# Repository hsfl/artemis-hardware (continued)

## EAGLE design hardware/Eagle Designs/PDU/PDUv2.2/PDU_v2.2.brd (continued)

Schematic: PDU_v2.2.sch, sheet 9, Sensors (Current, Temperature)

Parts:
C8, C29, C30, C37, C42, C61, C68, C69, C70, C71: 0.1 uF; 0805
C82: 0.1 uF; 0603-CAP
R26, R34, R36, R52, R54, R64, R65, R67, R76, R78: 3.3 k; 0805
R35, R39, R63, R66, R79, R80, R81, R84, R85, R88: 10; 0805
R53, R77, R87, R89, R90: 2 m; 0805
R61: 45.3 k; 0603-RES
R62: 10 k; 0603-RES
U15, U30, U31, U32, U33: INA219BIDR; SOIC127P599X175-8N
U18: TMP36FSZ; R_8_ADI

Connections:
AIN1: R61.1, R62.2; also elsewhere on the board
BUS_3V3: C8.1, C68.1, C69.1, C70.1, C71.1, C82.2, R26.1, R34.1, R36.1, R52.1, R54.1, R64.1, R65.1, R67.1, R76.1, R78.1, U15.1 (A1), U15.5 (VS), U18.5 (!SHUTDOWN), U18.8 (+VS), U30.5 (VS), U31.2 (A0), U31.5 (VS), U32.5 (VS), U33.5 (VS); also elsewhere on the board
CS_SOL1_VIN+: C30.1, R63.1, U30.8 (VIN+)
CS_SOL1_VIN-: C30.2, R66.1, U30.7 (VIN-)
CS_SOL2_VIN+: C37.1, R79.1, U31.8 (VIN+)
CS_SOL2_VIN-: C37.2, R80.1, U31.7 (VIN-)
CS_SOL3_VIN+: C42.1, R81.1, U32.8 (VIN+)
CS_SOL3_VIN-: C42.2, R88.1, U32.7 (VIN-)
CS_SOL4_VIN+: C61.1, R84.1, U33.8 (VIN+)
CS_SOL4_VIN-: C61.2, R85.1, U33.7 (VIN-)
CS_VBATT: R35.2, R53.2; also elsewhere on the board
CS_VBATT_VIN+: C29.1, R35.1, U15.8 (VIN+)
CS_VBATT_VIN-: C29.2, R39.1, U15.7 (VIN-)
GND: C8.2, C68.2, C69.2, C70.2, C71.2, C82.1, R62.1, U15.2 (A0), U15.6 (GND), U18.4 (GND), U30.1 (A1), U30.2 (A0), U30.6 (GND), U31.1 (A1), U31.6 (GND), U32.1 (A1), U32.6 (GND), U33.1 (A1), U33.6 (GND); also elsewhere on the board
I2C1_SCL: R36.2, R54.2, R64.2, R67.2, R78.2, U15.4 (SCL), U30.4 (SCL), U31.4 (SCL), U32.4 (SCL), U33.2 (A0), U33.4 (SCL); also elsewhere on the board
I2C1_SDA: R26.2, R34.2, R52.2, R65.2, R76.2, U15.3 (SDA), U30.3 (SDA), U31.3 (SDA), U32.2 (A0), U32.3 (SDA), U33.3 (SDA); also elsewhere on the board
unnamed: R61.2, U18.1 (VOUT)
SOLAR_IN1: R63.2, R77.2; also elsewhere on the board
SOLAR_IN1_LOAD: R66.2, R77.1; also elsewhere on the board
SOLAR_IN2: R79.2, R87.2; also elsewhere on the board
SOLAR_IN2_LOAD: R80.2, R87.1; also elsewhere on the board
SOLAR_IN3: R81.2, R89.2; also elsewhere on the board
SOLAR_IN3_LOAD: R88.2, R89.1; also elsewhere on the board
SOLAR_IN4: R84.2, R90.2; also elsewhere on the board
SOLAR_IN4_LOAD: R85.2, R90.1; also elsewhere on the board
VBATT: R39.2, R53.1; also elsewhere on the board

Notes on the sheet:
All cap/res in current sensor circuit is 0805 size.
All cap/res in temp sensor is 0603 size.
Analog Temperature Sensor
Current Sensor (VBATT)
Current Sensor (Solar Panels)

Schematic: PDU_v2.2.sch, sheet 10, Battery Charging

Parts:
C10, C12, C18, C91: 0.1 uF; 0805
C14, C39: 10 uF; 0805
C38: 4.7 uF; 0805
C40, C41: 1 uF; 0805
D1: CMDSH-3TR; SOD2512X110N
D3, D5: MBR230S1F; CR_0LSFT1G_ONS
D6, D7, D8, D9, D10, D11, D12: PMEG10020ELRX; CFP3_SOD123W_NEX
D13: LED_0805
J18: 5037630491; CON_5037630491
L2: AIML-0805-150K-T; AIML-0805_ABR
R27: 3 k; 0805
R28: 6.04 k; 0805
R29: 0; 0805
R37: 26.7 k; 0805
R55: 169 k; 0805
R56: 28.4k; 0603-RES
R91, R95: 1; 0805
R92, R94: 3.01 k; 0805
R96: 5.1 k; 0805
U20: LTC4012IUFPBF; QFN50P400X400X80-21N
U28: SI4431BDY-T1-E3; SOIC-8_SI
U29: AO4818B; SOIC8_NARROW_VIS

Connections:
5V_USB_CHRG: D12.2 (12); also elsewhere on the board
BATT_CHRG: C39.1, D5.1, R94.2, R95.1, U20.11 (BAT); also elsewhere on the board
BGATE: U20.16 (BGATE), U29.4 (2)
CHRG: D13.2, U20.7 (~CHRG); also elsewhere on the board
GND: C14.2, C38.2, C39.2, C40.2, C41.2, C91.2, J18.2, J18.4, J18.5, J18.6, R28.1, R37.1, R56.1, U20.21 (GND); also elsewhere on the board
INFET: U20.3 (INFET), U28.4 (G)
INH_SW1_COM: D6.1 (11), D7.1 (11), D8.1 (11), D9.1 (11), D10.1 (11), D11.1 (11), D12.1 (11), J18.1
INH_SW1_NC: C91.1, J18.3, R27.2, U20.4 (DCIN), U28.5 (D_2), U28.6 (D_3), U28.7 (D_4), U28.8 (D)
ITH: C10.1, U20.12 (ITH)
unnamed: D13.1, R27.1
unnamed: C10.2, R28.2
unnamed: C12.2, R96.1, U20.1 (CLN)
unnamed: R29.1, U20.20 (BOOST)
unnamed: C40.1, C41.1, D1.A, U20.17 (INTVDD)
unnamed: C18.1, D1.C, R29.2
unnamed: R92.1, U20.15 (CSP)
unnamed: R94.1, U20.14 (CSN)
unnamed: C38.1, R37.2, U20.13 (PROG)
unnamed: R55.1, U20.10 (FBDIV)
unnamed: R55.2, R56.2, U20.9 (VFB)
R_SENSE_R_IN1: L2.1, R92.2, R95.2
S2: D3.1, U29.2 (1)
SHDN: U20.6 (~SHDN); also elsewhere on the board
SOLAR_IN1_LOAD: D6.2 (12); also elsewhere on the board
SOLAR_IN2_LOAD: D7.2 (12); also elsewhere on the board
SOLAR_IN3_LOAD: D8.2 (12); also elsewhere on the board
SOLAR_IN4_LOAD: D9.2 (12); also elsewhere on the board
SOLAR_IN5: D10.2 (12); also elsewhere on the board
SOLAR_IN6: D11.2 (12); also elsewhere on the board
SW: C18.2, D3.2, L2.2, U20.18 (SW), U29.3, U29.6 (8), U29.7
TGATE: U20.19 (TGATE), U29.1 (4)
U2_S: C12.1, R91.1, U20.2 (CLP), U28.1 (S_2), U28.2 (S_3), U28.3 (S)
VBATT: C14.1, D5.2, R91.2, R96.2, U29.5 (6), U29.8 (5); also elsewhere on the board

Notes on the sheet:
All cap/res are 0603 size unless indicated otherwise.
Battery Charger Controller
Solar Cell Inhibit Switch Connectors
(From) Solar Panel Connectors
0805
~ACP left floating when unused (pg. 8)
*use AIML-0805-100K-T for 10 uH (0805) *use AIML-0805-150K-T for 15 uH (0805)
*From MCU
*To MCU
*Power to System Specifically, VBATT supplies PDU
Signal generated from MCU into LTC4012's Pin => *From MCU Signal generated from LTC4012's Pin into MCU => *To MCU
RC Circuit
BATT_CHRG is supplied by Batteries on PyCubed Battery Board
INH_SW1_NC = "SOLAR_VCC" Solar Input connected to Solar Cell Inhibit Switch
Two 1 uF Cap in Parallel = 2 uF Tot Cap
0603
~ICL left floating when unused (pg. 8)
(RIN1)
(RIN2)
(RSENSE)
LED (BATT CHRG)

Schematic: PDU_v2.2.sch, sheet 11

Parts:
J15: 5037630291; CON_5037630291

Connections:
CS_VBATT: J15.2; also elsewhere on the board
GND: J15.3, J15.4; also elsewhere on the board
PY_VBATT: J15.1; also elsewhere on the board

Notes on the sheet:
Insert Before Flight
PY_VBATT: Power source directly from PyCubed Battery Board CS_VBATT: Power source goes directly to current sensor for readings

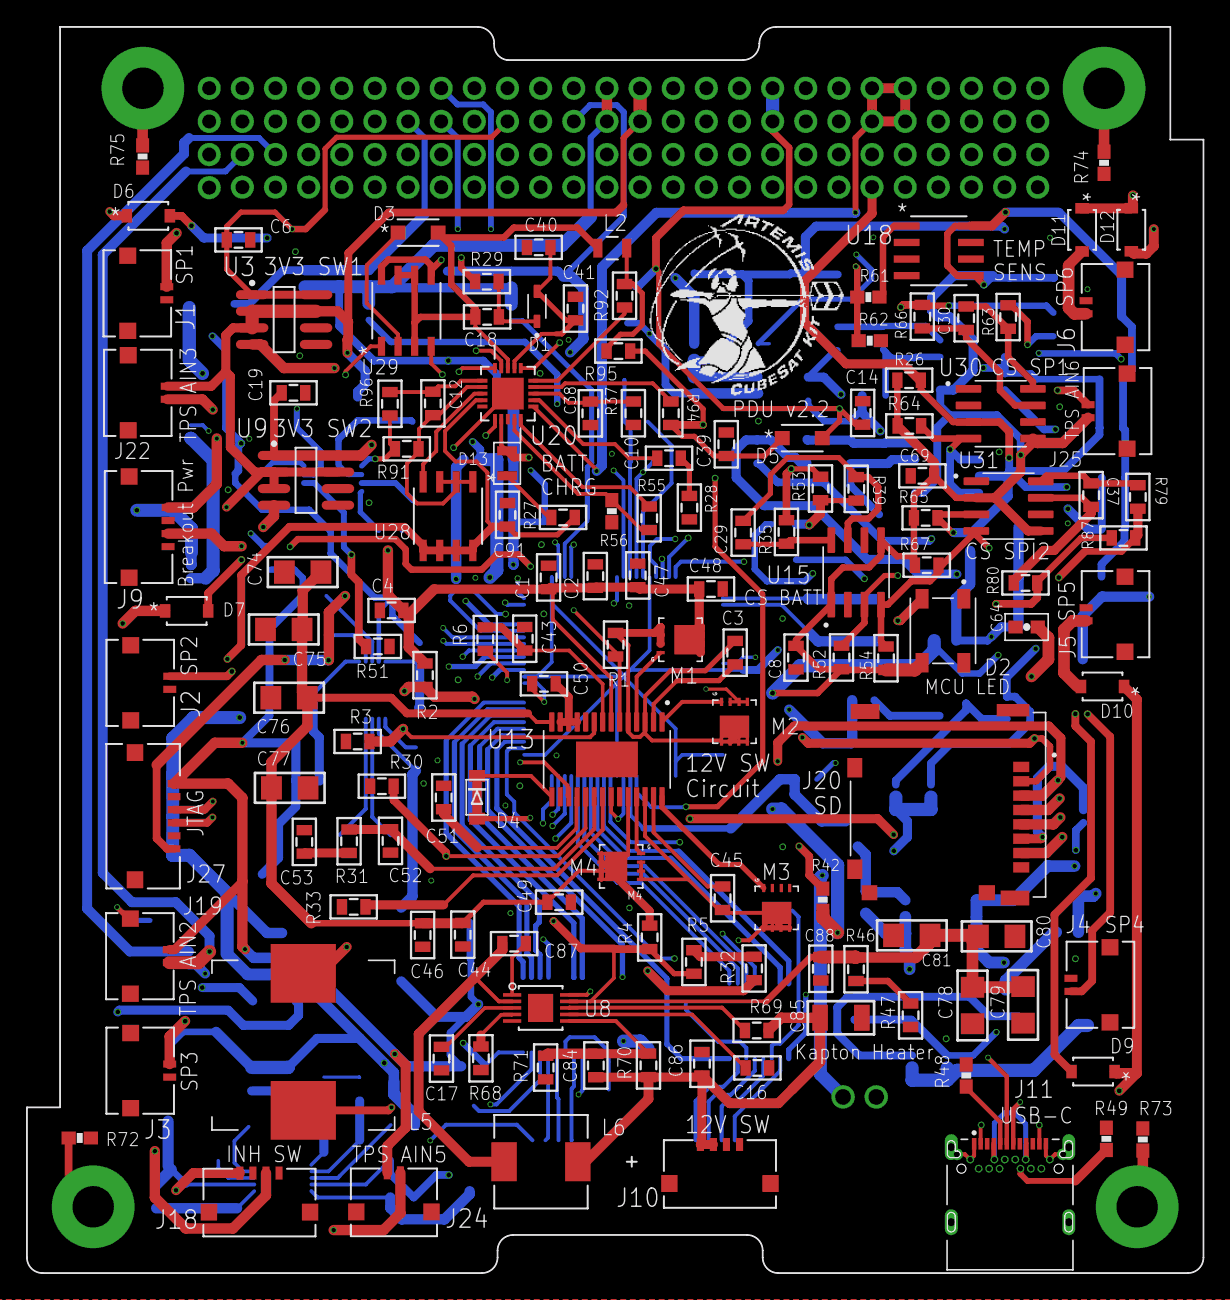
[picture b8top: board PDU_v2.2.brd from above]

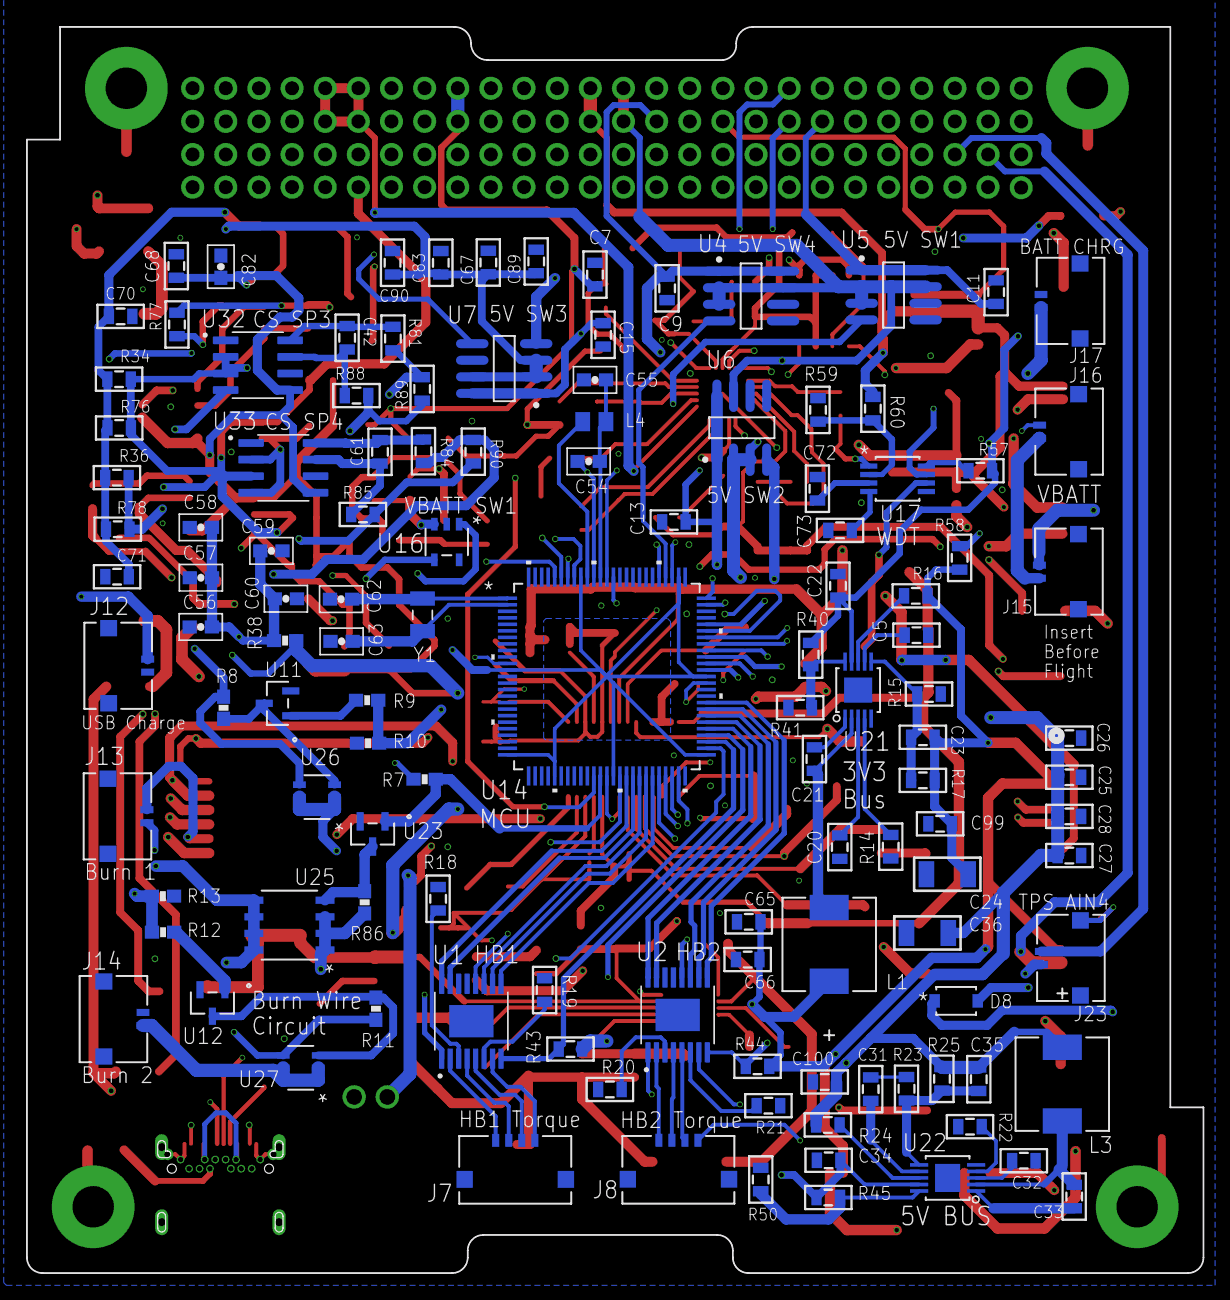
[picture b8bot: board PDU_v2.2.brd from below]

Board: 4 copper layers, 90.2 x 95.5 mm, 267 parts (121 on the bottom side), 187 nets.

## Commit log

2020-08-04 Transfer repo
2020-08-04 Scripts
2020-09-28 Removed doxygen output
2020-11-10 Create CAD model
2020-11-10 Rename README to README.md
2020-11-10 Rename README.md to README.txt
2020-11-12 Updated deploy
2020-12-08 Moved hardware files
2021-02-19 organizing the hardware folder, adding an Eagle folder for our designs
2021-02-19 Adding BOM
2021-02-19 Surface mount connectors connected to ground
2021-02-19 Moved solar panel boards to Eagle folder, deleted redudant OBC files
2021-02-26 OBC Board changes
    Switched out thru-hole connectors with Molex connectors; added ethernet and USB OTG connectors from BBB to OBC board and ethernet/USB OTG external connectors
2021-02-26 Removed unnecessary OBC backup files
2021-03-01 Added payload board Eagle files
2021-03-06 Edited payload board, created payload and bbb obc BOM
2021-03-09 Update payload board
2021-03-09 Update Payload board file
2021-03-09 Payload board changes
2021-03-09 Updated solar panel boards
2021-03-10 Solar panel board changes
    Added temp sensor and external connector to solar panel board; updated solar panel board BOM
2021-03-19 Added antenna board Eagle files and BOM
2021-04-20 Uploaded Eagle project files
2021-05-06 Uploaded Solar Panel Board v2
2021-05-06 Added values to resistors and capacitors
    Payload - added 3.3k value to pullup resistors for H-bridges
    Solar Panel Board - added 0.1uF value to capacitor for temp sensor
2021-05-06 Updated BOMs and edited Solar Panel Board v2
2021-05-07 Add files via upload
    Edited Solar Panel Board v2
2021-05-29 Uploaded H-bridge library and design block files
2021-05-29 added PDU v2 Eagle files and Artemis Library
2021-06-01 updated PDU v2 Eagle files and Artemis Library
2021-06-04 updated PDU v2 H Bridge Circuit Design
2021-06-04 Uploaded Eagle libraries
2021-06-07 Updated Solar Panel BOM
2021-06-11 updated PDU v2 and Artemis Library
2021-06-22 updated PDU v2 Microprocessor schematic
2021-06-29 updated PDU v2
2021-06-30 Updated antenna and solar panel boards.
2021-07-01 updated PDU v2 schematic
2021-07-01 Updated antenna and solar panel boards
2021-07-09 updated PDU v2 (pre-routing)
2021-07-14 Uploaded OBC version 2
2021-07-27 Changed connectors for RBF pin and moved in connectors that interfered with structure.
2021-07-30 updated PDU v2 (Routing Rough Draft complete)
2021-08-10 OBC version 3 is finally here
2021-08-11 Revised OBC v3 and BB v2
2021-08-13 made minor changes to the OBC and BB
2021-09-02 fixed naming issues
2021-09-03 uploaded completed PDU v2
2021-09-09 made improvements to the solar panel board and included cam outputs
2021-09-11 completed PDU v2
2021-10-01 Artemis V1.2 R2
2021-10-06 uploaded Camera Mount Board schem and board; removed PDU v2 screw terminal
2021-10-12 replaced PDU v2 terminal with Conn Header 0.1'
2021-10-12 Created OBC_v4
2021-10-12 Uploaded OBC_v4 BOM
2021-10-12 Solar panel board v6
2021-10-13 Updated OBC and Solar Panel boards
2021-10-14 added HSFL stencil logo to Camera Mount Panel Board
2021-10-16 OBC v4 edits
2021-11-09 Added Eagle files for EPET payload
2021-11-09 Added antenna board v3, removed extra antenna board v2 files
2021-11-10 Uploaded solar panel board v6.1
2021-11-10 Battery board text changes
2021-11-13 Updated scintillator detector PCB
2021-11-15 Updated solar panel board temp sensor circuit
2021-11-15 Edited temp sensor circuit on battery board
2021-11-15 Updated temp sensor circuit for scintillator pcb
2021-11-15 Changed scintillator temp sensor
2021-11-17 Scintillator detector edits
2021-11-18 Added text to bottom and top of board to denote connectors + temp sensor/torque coils
2021-11-24 updated PDU v2, added Battery Charging Circuit design block
2021-11-30 added PDU v2 Revisions
2021-12-01 Edited detector pcb and created battery charging circuit board
2021-12-07 updated OBC v4 with Teensy Rough Draft
2021-12-08 updated OBC v4.1; verified & updated Battery Charging Circuit
2021-12-08 Finalized PDU Battery Charging Circuit Design And Added Gerber Files
2021-12-10 Edited antenna board and battery board
2021-12-15 Latest CAD update
2021-12-22 Completed OBC v4.1 (Finished); Updated PDU v2.1 (Unfinished)
2021-12-22 Updated OBC v4.1
2021-12-24 updated OBC v4.1. with revision feedback
2021-12-30 Updated antenna board
2022-01-05 Added microUSB connector to antenna board
2022-01-06 uploaded Chris Noon's server and client
2022-01-07 Made edits to solar panel, antenna, battery boards
2022-01-19 completed PDU v2.1 revisions 01/18/2022 and did minor changes to OBC v4.1
2022-01-20 did OBC v4.1 revisions (replaced Antenna connector); uploaded OBC Eagle Library
2022-02-03 did OBC and PDU revisions (02/03/2022)
2022-02-08 updated PDU v2.1 (02/08/2022) before major changes
2022-02-15 updated OBC v4.20 (02/15/2022)
2022-02-18 finalized OBC v4.20; updated PDU v2.1
2022-02-18 revised and finalized OBC v4.20, added OBC v4.20 BOM and Gerber Files
2022-02-23 Antenna board edits
2022-02-25 updated PDU v2.1 (ongoing board cleanup)
2022-03-01 completed PDU v2.1 (awaiting feedback)
2022-03-08 finalized PDU v2.1 and generated Gerber Files
2022-03-15 added Kapton Heater Connector (device) to PDU v2.1
2022-03-17 Switched the Teensy UART pins on OBCv4.21
2022-03-30 Antenna board silkscreen edits
2022-04-08 Updated OBC v4.21 with 2 Radios, Added SPI to PC 104 Header, Uploaded Radio Devices Eagle Library
2022-04-08 Corrected SPI Connections to PC 104 Header
2022-04-14 fixed OBC modular radio Radio Reset connection
2022-04-21 uploaded official OBC v4.21
2022-05-11 Created PDU v2.2; First edit
2022-07-27 created OBC v4.22 and uploaded revised Teensy Library
2022-07-27 updated PDU v2.2
2022-07-29 Antenna Board hole changes
2022-08-31 Eagle battery board
2022-09-10 completed OBC v4.23
2022-09-10 updated and finalized OBC V4.23
2022-09-23 Added v2 boards
2022-09-23 Removed unnecessary v2 backup Eagle files; added newest OBC revision
2022-10-12 OBC Organization
2022-11-02 OBC 4.24
2022-11-02 OBC_V4.24
2022-11-03 added power labels to R8, R9 of OBC V4.24
2022-12-01 OBC V4.24
2022-12-02 cleaned up a wire stub on OBC 4.24 and copied OBC for RF with ground plane
2022-12-02 renamed OBC 4.24_RFplane
2022-12-03 Added RF plane to OBCv4.24
2022-12-03 changed radio power supply from 5V_bus to SW_3V3_2 on both the OBCv2.24 and OBCv2.24_RFplane. Added ground station board.
2022-12-06 Renamed and reorganized Artemis v2 boards
2022-12-06 Created an Artemis v2 battery board
2022-12-08 add PDUv2.0 board and schematic
2022-12-08 Updated Artemis v2 EAGLE libraries and removed
2022-12-09 Updated Artemis v2 EAGLE library, solar panel board, and antenna board
2023-02-03 added VIA to GND Plane for PDU V2.2
2023-02-16 Swapped the antenna pad for the MCX connector on the ground station board. Created the mock transmission board which is a radio, teensy and antenna.
2023-02-17 Added RF ground plane to ground station board.
2023-02-28 Modified pin configuration on the ground station board to match OBC 4.24.
2023-03-01 fixed OBC, PDU for Manufacturing Order
2023-03-14 fixed PDU for manufacturing
2023-03-23 Fixed RF ground station board... again.
2023-05-11 cleaned up
2023-05-11 fix broken image paths and update website url
2023-05-12 fix broken image paths, update website url, and clean up
2023-05-18 Battery Board V2 changes
2023-05-18 Battery Board V3 Changes
2023-05-19 Solar Panel and Antenna Board Edits
2023-06-21 Board updates
2023-08-31 ArtemisR4
    Updated Artemis Structure for lab.
2023-08-31 Updated Structure Model for Lab
2023-11-21 Add files via upload
    Thermal Desktop files
2024-01-19 reorganize
2024-02-29 add simulator
2024-02-29 add detumbling-simulator as a git module
